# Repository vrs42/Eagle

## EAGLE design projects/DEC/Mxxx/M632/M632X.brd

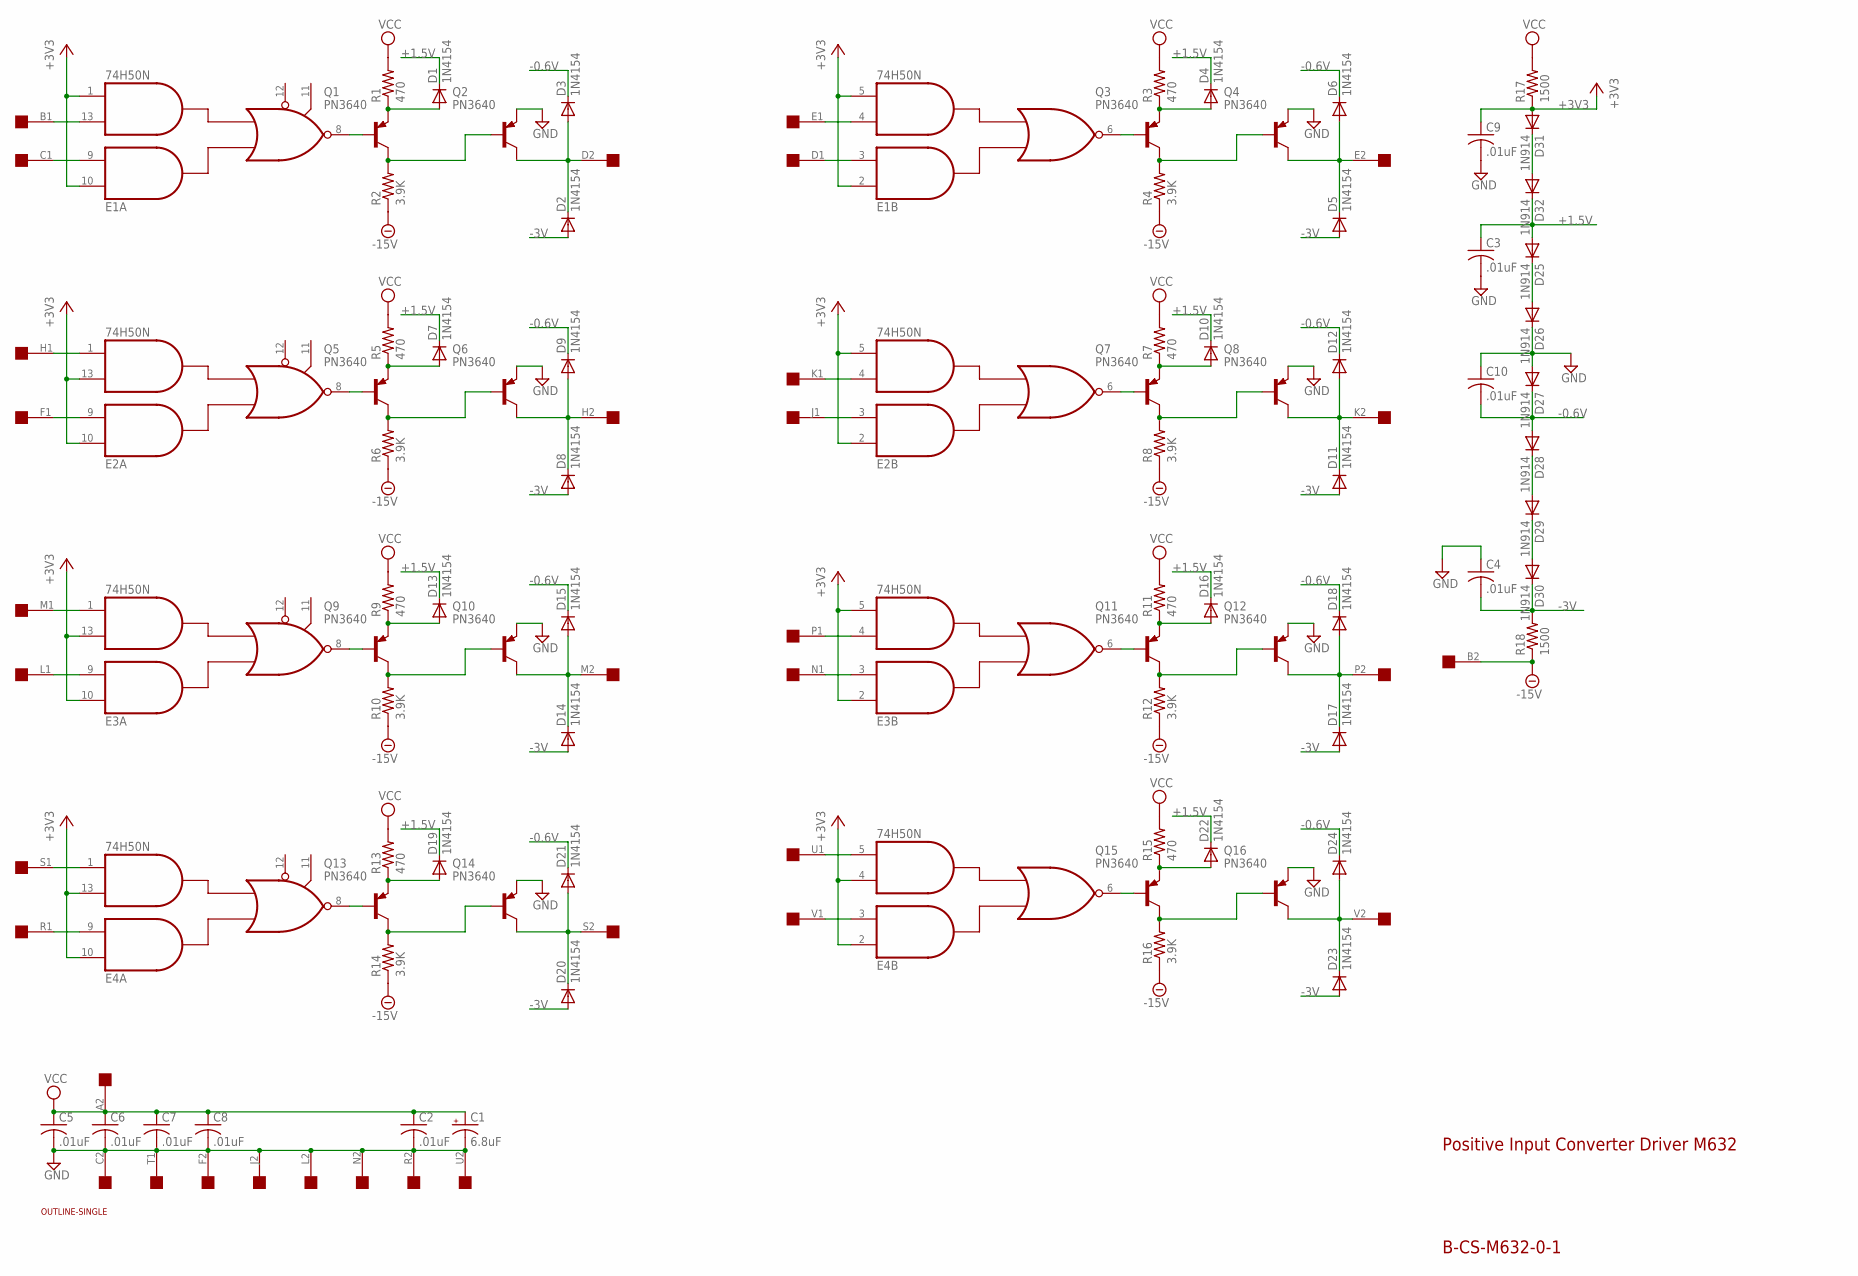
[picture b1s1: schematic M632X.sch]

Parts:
C1: 6.8uF; E12-8
C2, C3, C4, C5, C6, C7, C8, C9, C10: .01uF; C050-025X075
D1, D2, D3, D4, D5, D6, D7, D8, D9, D10, D11, D12, D13, D14, D15, D16, D17, D18, D19, D20, D21, D22, D23, D24: 1N4154; DO35-10
D25, D26, D27, D28, D29, D30, D31, D32: 1N914; DO35-10
E1, E2, E3, E4: 74H50N; DIL14
Q1, Q2, Q3, Q4, Q5, Q6, Q7, Q8, Q9, Q10, Q11, Q12, Q13, Q14, Q15, Q16: PN3640; TO39
R1, R3, R5, R7, R9, R11, R13, R15: 470; 0207/10
R2, R4, R6, R8, R10, R12, R14, R16: 3.9K; 0207/10
R17, R18: 1500; 0207/10
U$1: SINGLE; EDGE-CON2
U$4: OUTLINE-SINGLE; SINGLE

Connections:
+1.5V: C3.1, D1.C, D4.C, D7.C, D10.C, D13.C, D16.C, D19.C, D22.C, D25.A, D32.C
+3V3: C9.1, D31.A, E1.1 (I4), E1.2 (I1), E1.5 (I4), E1.10 (I1), E2.2 (I1), E2.5 (I4), E2.10 (I1), E2.13 (I3), E3.2 (I1), E3.5 (I4), E3.10 (I1), E3.13 (I3), E4.2 (I1), E4.4 (I3), E4.10 (I1), E4.13 (I3), R17.1
-0.6V: C10.2, D3.C, D6.C, D9.C, D12.C, D15.C, D18.C, D21.C, D24.C, D27.C, D28.A
-3V: C4.2, D2.A, D5.A, D8.A, D11.A, D14.A, D17.A, D20.A, D23.A, D30.C, R18.2
-15V: R2.1, R4.1, R6.1, R8.1, R10.1, R12.1, R14.1, R16.1, R18.1, U$1.B2
GND: C1.-, C2.2, C3.2, C4.1, C5.2, C6.2, C7.2, C8.2, C9.2, C10.1, D26.C, D27.A, E1.7 (GND), E2.7 (GND), E3.7 (GND), E4.7 (GND), Q2.1 (E), Q4.1 (E), Q6.1 (E), Q8.1 (E), Q10.1 (E), Q12.1 (E), Q14.1 (E), Q16.1 (E), U$1.C2, U$1.F2, U$1.J2, U$1.L2, U$1.N2, U$1.R2, U$1.T1, U$1.U2
unnamed: E2.3 (I2), U$1.J1
unnamed: E2.4 (I3), U$1.K1
unnamed: E1.9 (I2), U$1.C1
unnamed: E1.13 (I3), U$1.B1
unnamed: E4.1 (I4), U$1.S1
unnamed: E4.9 (I2), U$1.R1
unnamed: E1.8 (O), Q1.2 (B)
unnamed: Q1.3 (C), Q2.2 (B), R2.2
unnamed: E2.8 (O), Q5.2 (B)
unnamed: D7.A, Q5.1 (E), R5.1
unnamed: D2.C, D3.A, Q2.3 (C), U$1.D2
unnamed: Q5.3 (C), Q6.2 (B), R6.2
unnamed: D8.C, D9.A, Q6.3 (C), U$1.H2
unnamed: E4.3 (I2), U$1.V1
unnamed: E4.5 (I4), U$1.U1
unnamed: E3.1 (I4), U$1.M1
unnamed: E3.9 (I2), U$1.L1
unnamed: E3.8 (O), Q9.2 (B)
unnamed: D13.A, Q9.1 (E), R9.1
unnamed: Q9.3 (C), Q10.2 (B), R10.2
unnamed: D14.C, D15.A, Q10.3 (C), U$1.M2
unnamed: E4.8 (O), Q13.2 (B)
unnamed: D19.A, Q13.1 (E), R13.1
unnamed: Q13.3 (C), Q14.2 (B), R14.2
unnamed: D20.C, D21.A, Q14.3 (C), U$1.S2
unnamed: E1.6 (O), Q3.2 (B)
unnamed: D4.A, Q3.1 (E), R3.1
unnamed: Q3.3 (C), Q4.2 (B), R4.2
unnamed: E1.4 (I3), U$1.E1
unnamed: E1.3 (I2), U$1.D1
unnamed: D5.C, D6.A, Q4.3 (C), U$1.E2
unnamed: E2.6 (O), Q7.2 (B)
unnamed: E2.1 (I4), U$1.H1
unnamed: E3.3 (I2), U$1.N1
unnamed: E3.4 (I3), U$1.P1
unnamed: E2.9 (I2), U$1.F1
unnamed: D10.A, Q7.1 (E), R7.1
unnamed: Q7.3 (C), Q8.2 (B), R8.2
unnamed: D11.C, D12.A, Q8.3 (C), U$1.K2
unnamed: E3.6 (O), Q11.2 (B)
unnamed: D1.A, Q1.1 (E), R1.1
unnamed: D16.A, Q11.1 (E), R11.1
unnamed: Q11.3 (C), Q12.2 (B), R12.2
unnamed: D17.C, D18.A, Q12.3 (C), U$1.P2
unnamed: E4.6 (O), Q15.2 (B)
unnamed: D22.A, Q15.1 (E), R15.1
unnamed: Q15.3 (C), Q16.2 (B), R16.2
unnamed: D23.C, D24.A, Q16.3 (C), U$1.V2
unnamed: D25.C, D26.A
unnamed: D28.C, D29.A
unnamed: D31.C, D32.A
unnamed: D29.C, D30.A
VCC: C1.+, C2.1, C5.1, C6.1, C7.1, C8.1, E1.14 (VCC), E2.14 (VCC), E3.14 (VCC), E4.14 (VCC), R1.2, R3.2, R5.2, R7.2, R9.2, R11.2, R13.2, R15.2, R17.2, U$1.A2

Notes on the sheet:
Positive Input Converter Driver M632
B-CS-M632-0-1

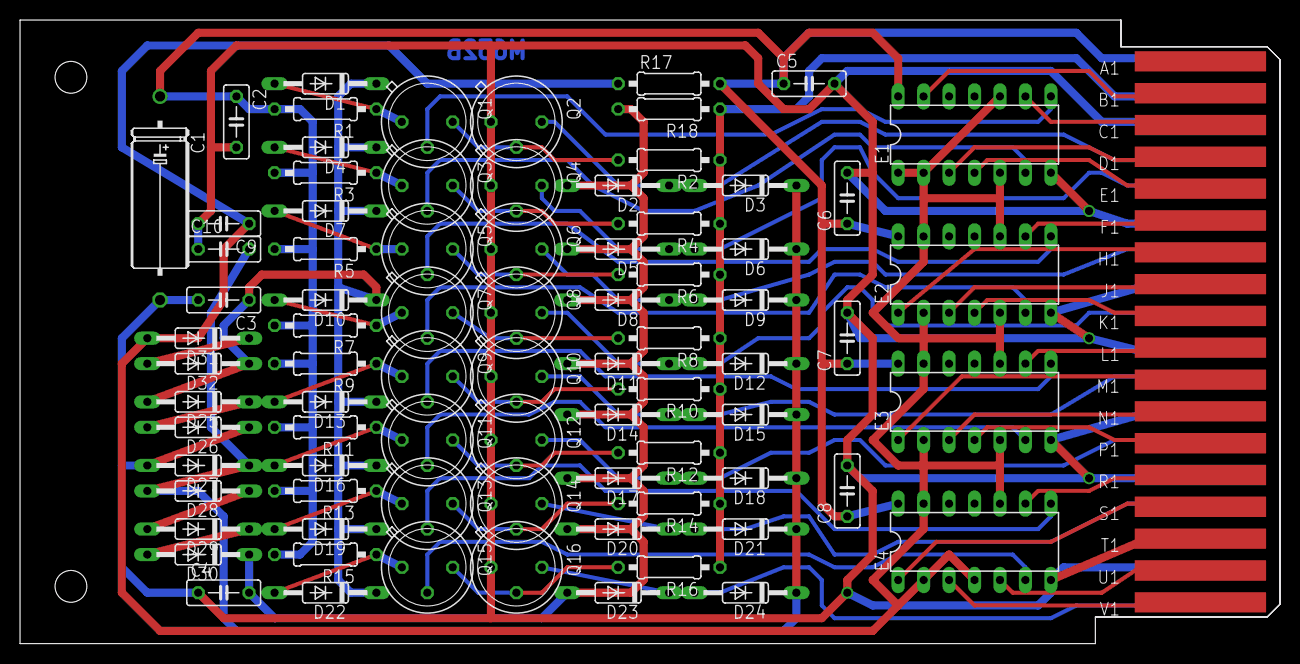
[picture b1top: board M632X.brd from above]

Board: 2 copper layers, 125.7 x 62.2 mm, 82 parts (0 on the bottom side), 59 nets.

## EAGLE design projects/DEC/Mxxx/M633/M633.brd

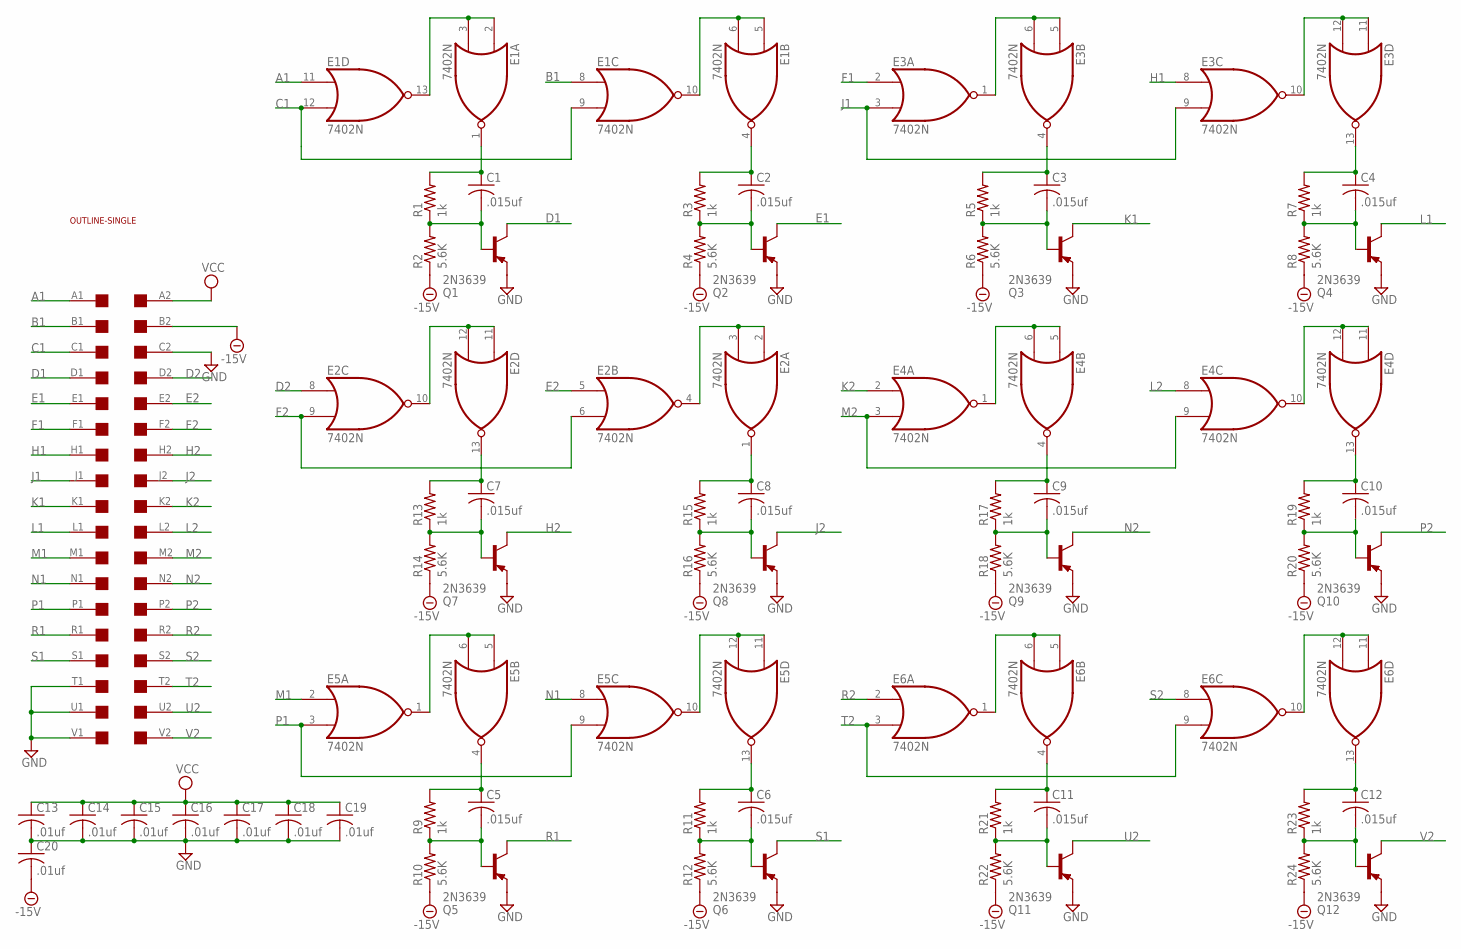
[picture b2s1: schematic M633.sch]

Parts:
C1, C2, C3, C4, C5, C6, C7, C8, C9, C10, C11, C12: .015uf; C050-025X075
C13, C14, C15, C16, C17, C18, C19, C20: .01uf; C050-025X075
E1, E2, E3, E4, E5, E6: 7402N; DIL14
Q1, Q2, Q3, Q4, Q5, Q6, Q7, Q8, Q9, Q10, Q11, Q12: 2N3639; TO39
R1, R3, R5, R7, R9, R11, R13, R15, R17, R19, R21, R23: 1k; 0207/10
R2, R4, R6, R8, R10, R12, R14, R16, R18, R20, R22, R24: 5.6K; 0207/10
U$1: SINGLE; EDGE-CON2
U$2: OUTLINE-SINGLE; SINGLE

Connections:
-15V: C20.2, R2.1, R4.1, R6.1, R8.1, R10.1, R12.1, R14.1, R16.1, R18.1, R20.1, R22.1, R24.1, U$1.B2
A1: E1.11 (I0), U$1.A1
B1: E1.8 (I0), U$1.B1
C1: E1.9 (I1), E1.12 (I1), U$1.C1
D1: Q1.3 (C), U$1.D1
D2: E2.8 (I0), U$1.D2
E1: Q2.3 (C), U$1.E1
E2: E2.5 (I0), U$1.E2
F1: E3.2 (I0), U$1.F1
F2: E2.6 (I1), E2.9 (I1), U$1.F2
GND: C13.2, C14.2, C15.2, C16.2, C17.2, C18.2, C19.2, C20.1, E1.7 (GND), E2.7 (GND), E3.7 (GND), E4.7 (GND), E5.7 (GND), E6.7 (GND), Q1.1 (E), Q2.1 (E), Q3.1 (E), Q4.1 (E), Q5.1 (E), Q6.1 (E), Q7.1 (E), Q8.1 (E), Q9.1 (E), Q10.1 (E), Q11.1 (E), Q12.1 (E), U$1.C2, U$1.T1, U$1.U1, U$1.V1
H1: E3.8 (I0), U$1.H1
H2: Q7.3 (C), U$1.H2
J1: E3.3 (I1), E3.9 (I1), U$1.J1
J2: Q8.3 (C), U$1.J2
K1: Q3.3 (C), U$1.K1
K2: E4.2 (I0), U$1.K2
L1: Q4.3 (C), U$1.L1
L2: E4.8 (I0), U$1.L2
M1: E5.2 (I0), U$1.M1
M2: E4.3 (I1), E4.9 (I1), U$1.M2
N1: E5.8 (I0), U$1.N1
N2: Q9.3 (C), U$1.N2
unnamed: E1.2 (I0), E1.3 (I1), E1.13 (O)
unnamed: C1.1, E1.1 (O), R1.2
unnamed: C1.2, Q1.2 (B), R1.1, R2.2
unnamed: C3.1, E3.4 (O), R5.2
unnamed: C2.1, E1.4 (O), R3.2
unnamed: C2.2, Q2.2 (B), R3.1, R4.2
unnamed: E1.5 (I0), E1.6 (I1), E1.10 (O)
unnamed: E2.10 (O), E2.11 (I0), E2.12 (I1)
unnamed: E2.2 (I0), E2.3 (I1), E2.4 (O)
unnamed: E4.1 (O), E4.5 (I0), E4.6 (I1)
unnamed: E4.10 (O), E4.11 (I0), E4.12 (I1)
unnamed: E6.10 (O), E6.11 (I0), E6.12 (I1)
unnamed: E6.1 (O), E6.5 (I0), E6.6 (I1)
unnamed: E5.10 (O), E5.11 (I0), E5.12 (I1)
unnamed: E5.1 (O), E5.5 (I0), E5.6 (I1)
unnamed: E3.10 (O), E3.11 (I0), E3.12 (I1)
unnamed: E3.1 (O), E3.5 (I0), E3.6 (I1)
unnamed: C4.1, E3.13 (O), R7.2
unnamed: C9.1, E4.4 (O), R17.2
unnamed: C10.1, E4.13 (O), R19.2
unnamed: C8.1, E2.1 (O), R15.2
unnamed: C7.1, E2.13 (O), R13.2
unnamed: C7.2, Q7.2 (B), R13.1, R14.2
unnamed: C8.2, Q8.2 (B), R15.1, R16.2
unnamed: C9.2, Q9.2 (B), R17.1, R18.2
unnamed: C10.2, Q10.2 (B), R19.1, R20.2
unnamed: C5.1, E5.4 (O), R9.2
unnamed: C5.2, Q5.2 (B), R9.1, R10.2
unnamed: C6.2, Q6.2 (B), R11.1, R12.2
unnamed: C11.2, Q11.2 (B), R21.1, R22.2
unnamed: C12.2, Q12.2 (B), R23.1, R24.2
unnamed: C6.1, E5.13 (O), R11.2
unnamed: C11.1, E6.4 (O), R21.2
unnamed: C12.1, E6.13 (O), R23.2
unnamed: C3.2, Q3.2 (B), R5.1, R6.2
unnamed: C4.2, Q4.2 (B), R7.1, R8.2
P1: E5.3 (I1), E5.9 (I1), U$1.P1
P2: Q10.3 (C), U$1.P2
R1: Q5.3 (C), U$1.R1
R2: E6.2 (I0), U$1.R2
S1: Q6.3 (C), U$1.S1
S2: E6.8 (I0), U$1.S2
T2: E6.3 (I1), E6.9 (I1), U$1.T2
U2: Q11.3 (C), U$1.U2
V2: Q12.3 (C), U$1.V2
VCC: C13.1, C14.1, C15.1, C16.1, C17.1, C18.1, C19.1, E1.14 (VCC), E2.14 (VCC), E3.14 (VCC), E4.14 (VCC), E5.14 (VCC), E6.14 (VCC), U$1.A2

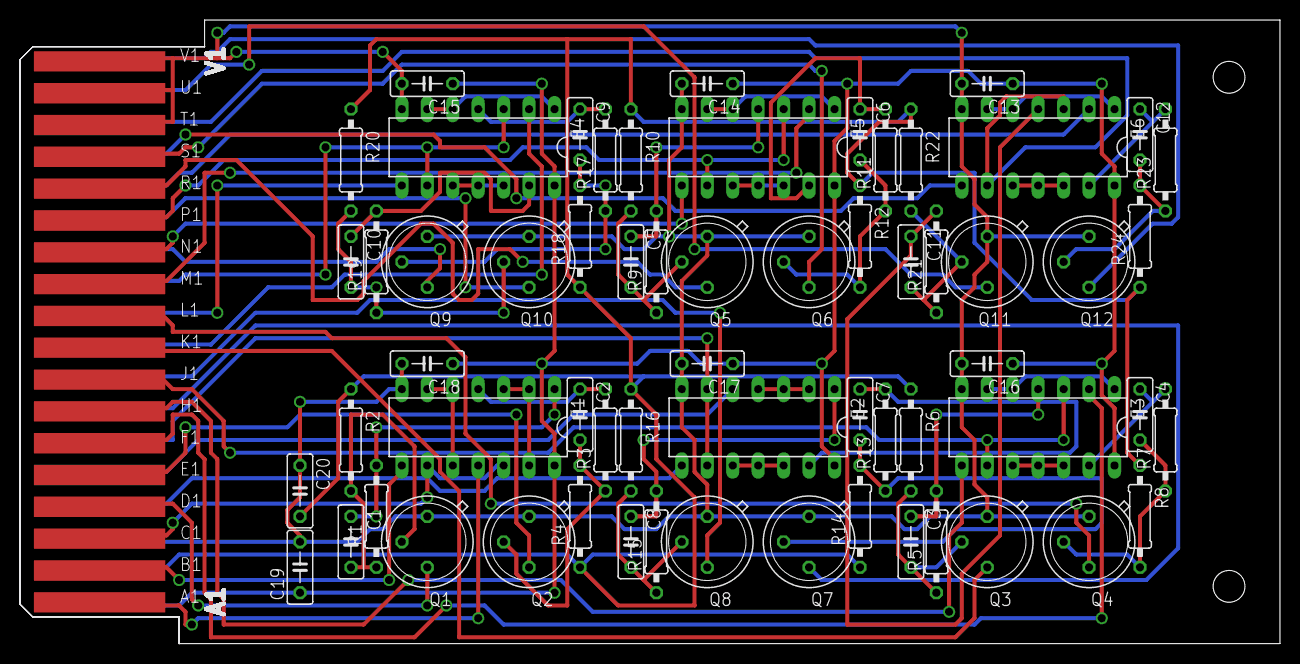
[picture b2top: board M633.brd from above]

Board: 2 copper layers, 125.7 x 62.2 mm, 64 parts (0 on the bottom side), 69 nets.

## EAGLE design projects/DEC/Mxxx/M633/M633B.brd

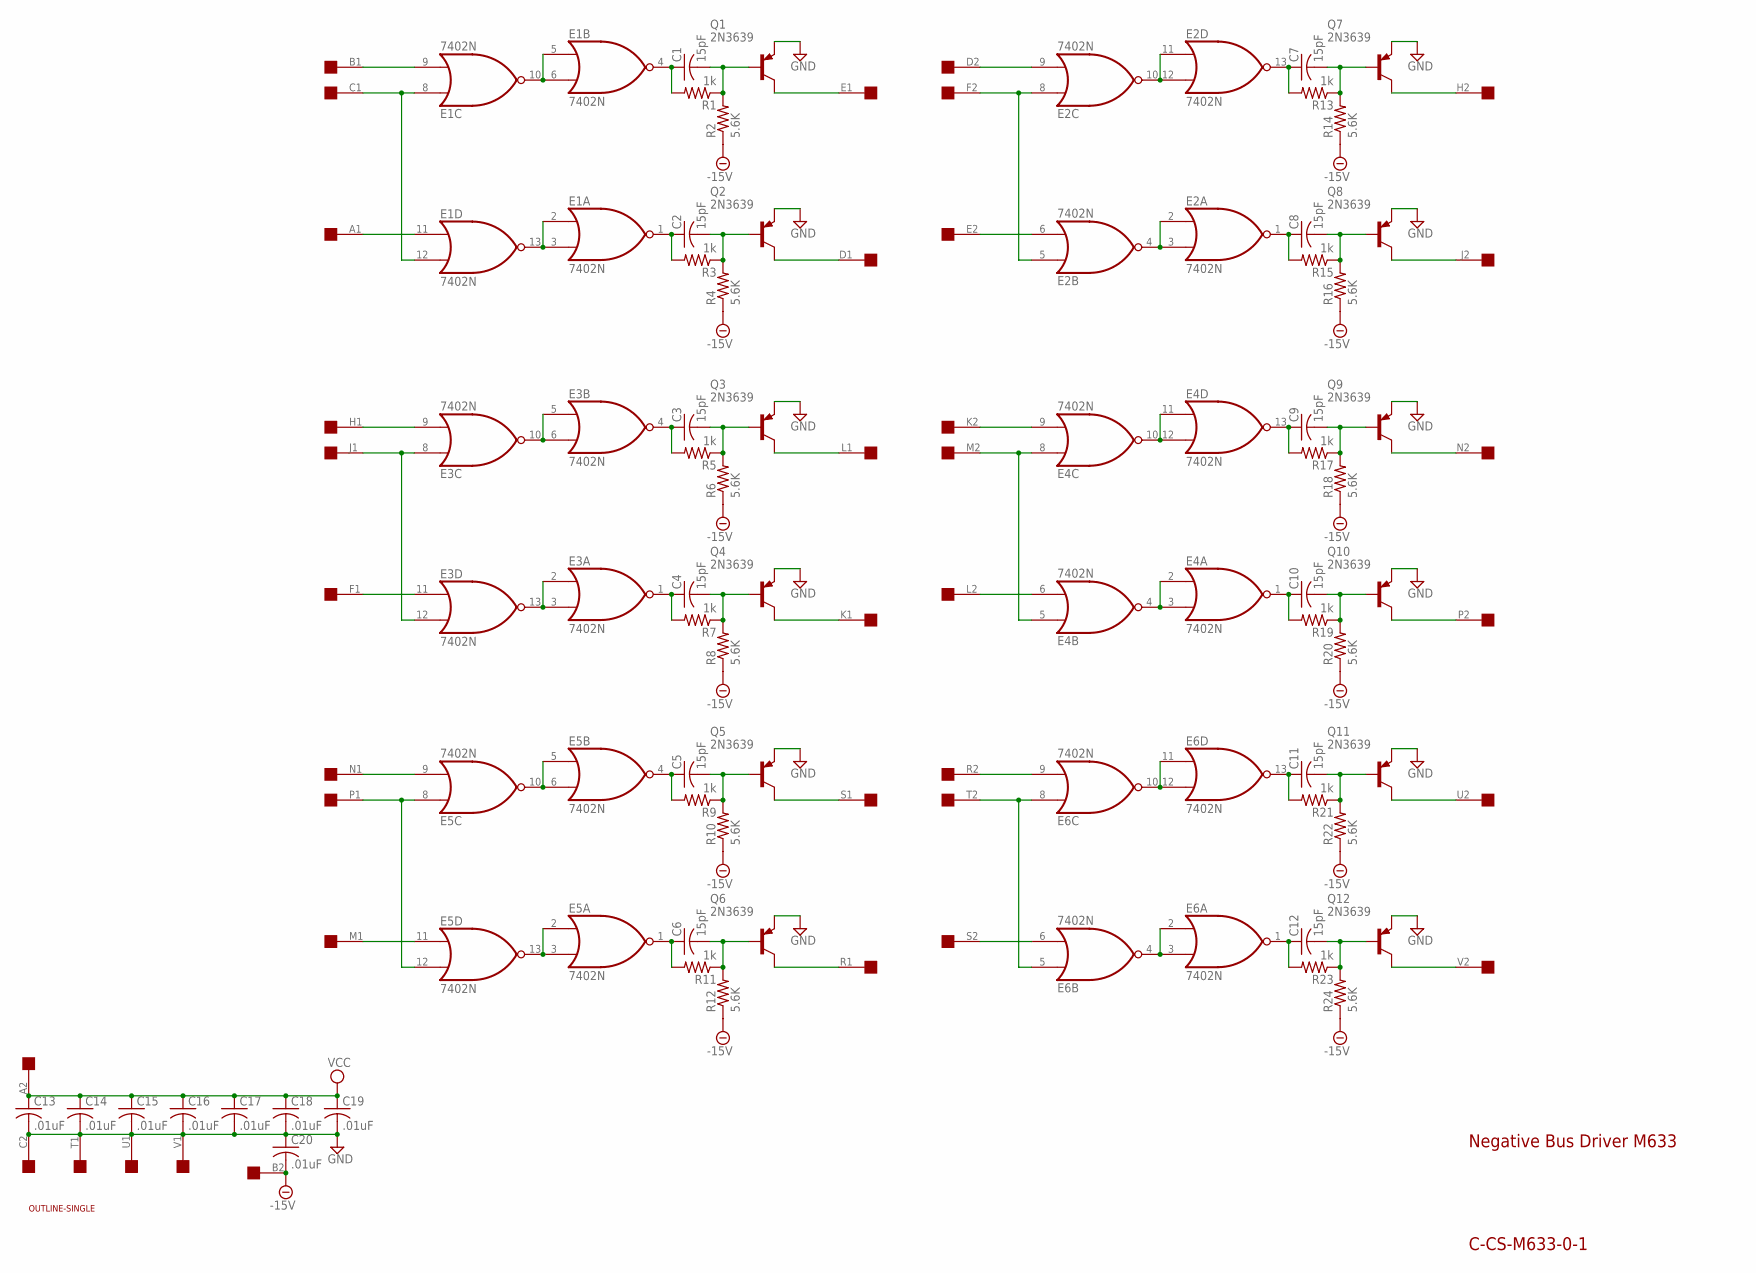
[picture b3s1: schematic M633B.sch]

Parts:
C1, C2, C3, C4, C5, C6, C7, C8, C9, C10, C11, C12: 15pF; C050-025X075
C13, C14, C15, C16, C17, C18, C19, C20: .01uF; C050-025X075
E1, E2, E3, E4, E5, E6: 7402N; DIL14
Q1, Q2, Q3, Q4, Q5, Q6, Q7, Q8, Q9, Q10, Q11, Q12: 2N3639; TO39
R1, R3, R5, R7, R9, R11, R13, R15, R17, R19, R21, R23: 1k; 0207/10
R2, R4, R6, R8, R10, R12, R14, R16, R18, R20, R22, R24: 5.6K; 0207/10
U$1: OUTLINE-SINGLE; SINGLE
U$4: SINGLE; EDGE-CON2

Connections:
-15V: C20.2, R2.1, R4.1, R6.1, R8.1, R10.1, R12.1, R14.1, R16.1, R18.1, R20.1, R22.1, R24.1, U$4.B2
GND: C13.2, C14.2, C15.2, C16.2, C17.2, C18.2, C19.2, C20.1, E1.7 (GND), E2.7 (GND), E3.7 (GND), E4.7 (GND), E5.7 (GND), E6.7 (GND), Q1.1 (E), Q2.1 (E), Q3.1 (E), Q4.1 (E), Q5.1 (E), Q6.1 (E), Q7.1 (E), Q8.1 (E), Q9.1 (E), Q10.1 (E), Q11.1 (E), Q12.1 (E), U$4.C2, U$4.T1, U$4.U1, U$4.V1
unnamed: E1.5 (I0), E1.6 (I1), E1.10 (O)
unnamed: C1.1, E1.4 (O), R1.2
unnamed: C1.2, Q1.2 (B), R1.1, R2.2
unnamed: E1.2 (I0), E1.3 (I1), E1.13 (O)
unnamed: E4.10 (O), E4.11 (I0), E4.12 (I1)
unnamed: C9.1, E4.13 (O), R17.2
unnamed: E4.2 (I0), E4.3 (I1), E4.4 (O)
unnamed: C10.1, E4.1 (O), R19.2
unnamed: C10.2, Q10.2 (B), R19.1, R20.2
unnamed: E4.5 (I0), E4.8 (I0), U$4.M2
unnamed: E4.9 (I1), U$4.K2
unnamed: C2.1, E1.1 (O), R3.2
unnamed: C2.2, Q2.2 (B), R3.1, R4.2
unnamed: E1.8 (I0), E1.12 (I1), U$4.C1
unnamed: E1.9 (I1), U$4.B1
unnamed: E1.11 (I0), U$4.A1
unnamed: Q2.3 (C), U$4.D1
unnamed: Q1.3 (C), U$4.E1
unnamed: E2.10 (O), E2.11 (I0), E2.12 (I1)
unnamed: C7.1, E2.13 (O), R13.2
unnamed: C7.2, Q7.2 (B), R13.1, R14.2
unnamed: E2.2 (I0), E2.3 (I1), E2.4 (O)
unnamed: E4.6 (I1), U$4.L2
unnamed: C8.1, E2.1 (O), R15.2
unnamed: C8.2, Q8.2 (B), R15.1, R16.2
unnamed: E2.5 (I0), E2.8 (I0), U$4.F2
unnamed: E2.9 (I1), U$4.D2
unnamed: E2.6 (I1), U$4.E2
unnamed: Q8.3 (C), U$4.J2
unnamed: Q7.3 (C), U$4.H2
unnamed: E3.5 (I0), E3.6 (I1), E3.10 (O)
unnamed: C3.1, E3.4 (O), R5.2
unnamed: Q10.3 (C), U$4.P2
unnamed: Q9.3 (C), U$4.N2
unnamed: C3.2, Q3.2 (B), R5.1, R6.2
unnamed: C9.2, Q9.2 (B), R17.1, R18.2
unnamed: E3.2 (I0), E3.3 (I1), E3.13 (O)
unnamed: C4.1, E3.1 (O), R7.2
unnamed: C4.2, Q4.2 (B), R7.1, R8.2
unnamed: E3.8 (I0), E3.12 (I1), U$4.J1
unnamed: E3.9 (I1), U$4.H1
unnamed: E3.11 (I0), U$4.F1
unnamed: Q4.3 (C), U$4.K1
unnamed: Q3.3 (C), U$4.L1
unnamed: E5.5 (I0), E5.6 (I1), E5.10 (O)
unnamed: C5.1, E5.4 (O), R9.2
unnamed: C5.2, Q5.2 (B), R9.1, R10.2
unnamed: E5.2 (I0), E5.3 (I1), E5.13 (O)
unnamed: C6.1, E5.1 (O), R11.2
unnamed: C6.2, Q6.2 (B), R11.1, R12.2
unnamed: E5.8 (I0), E5.12 (I1), U$4.P1
unnamed: E5.9 (I1), U$4.N1
unnamed: E5.11 (I0), U$4.M1
unnamed: Q6.3 (C), U$4.R1
unnamed: Q5.3 (C), U$4.S1
unnamed: E6.10 (O), E6.11 (I0), E6.12 (I1)
unnamed: C11.1, E6.13 (O), R21.2
unnamed: C11.2, Q11.2 (B), R21.1, R22.2
unnamed: E6.2 (I0), E6.3 (I1), E6.4 (O)
unnamed: C12.1, E6.1 (O), R23.2
unnamed: C12.2, Q12.2 (B), R23.1, R24.2
unnamed: E6.5 (I0), E6.8 (I0), U$4.T2
unnamed: E6.9 (I1), U$4.R2
unnamed: E6.6 (I1), U$4.S2
unnamed: Q12.3 (C), U$4.V2
unnamed: Q11.3 (C), U$4.U2
VCC: C13.1, C14.1, C15.1, C16.1, C17.1, C18.1, C19.1, E1.14 (VCC), E2.14 (VCC), E3.14 (VCC), E4.14 (VCC), E5.14 (VCC), E6.14 (VCC), U$4.A2

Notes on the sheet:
Negative Bus Driver M633
C-CS-M633-0-1

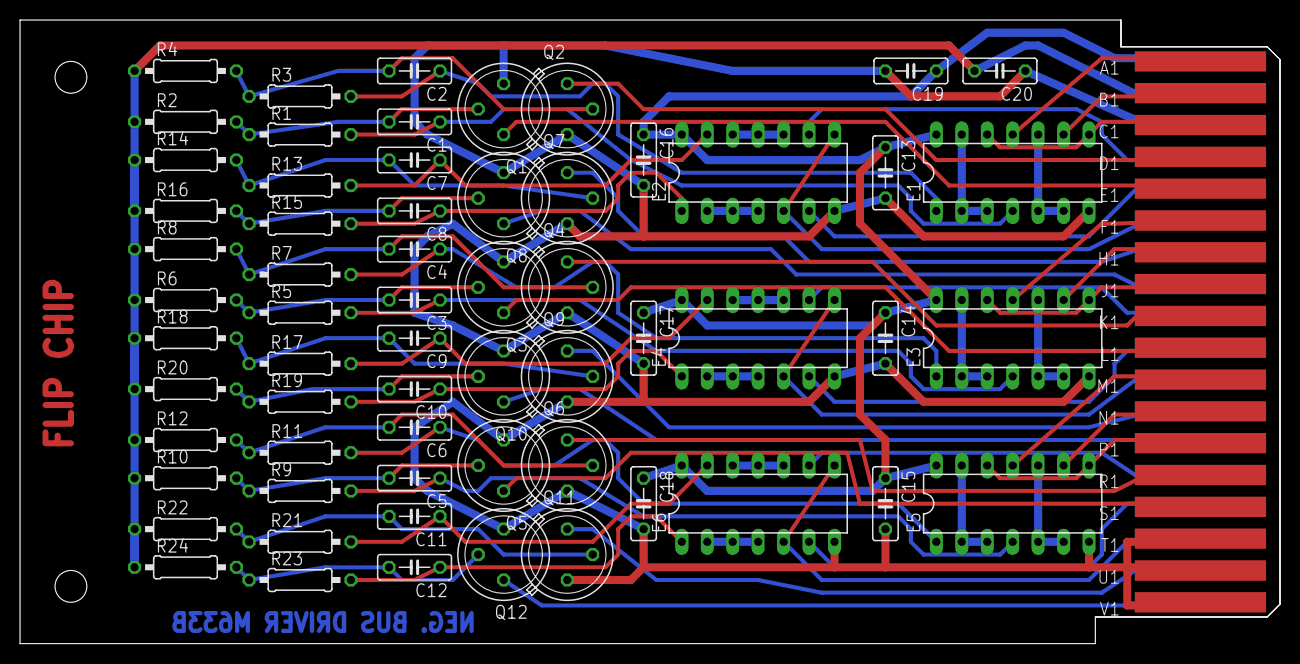
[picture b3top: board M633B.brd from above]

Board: 2 copper layers, 125.7 x 62.2 mm, 65 parts (0 on the bottom side), 69 nets.

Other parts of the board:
U$2: FLIPCHIP

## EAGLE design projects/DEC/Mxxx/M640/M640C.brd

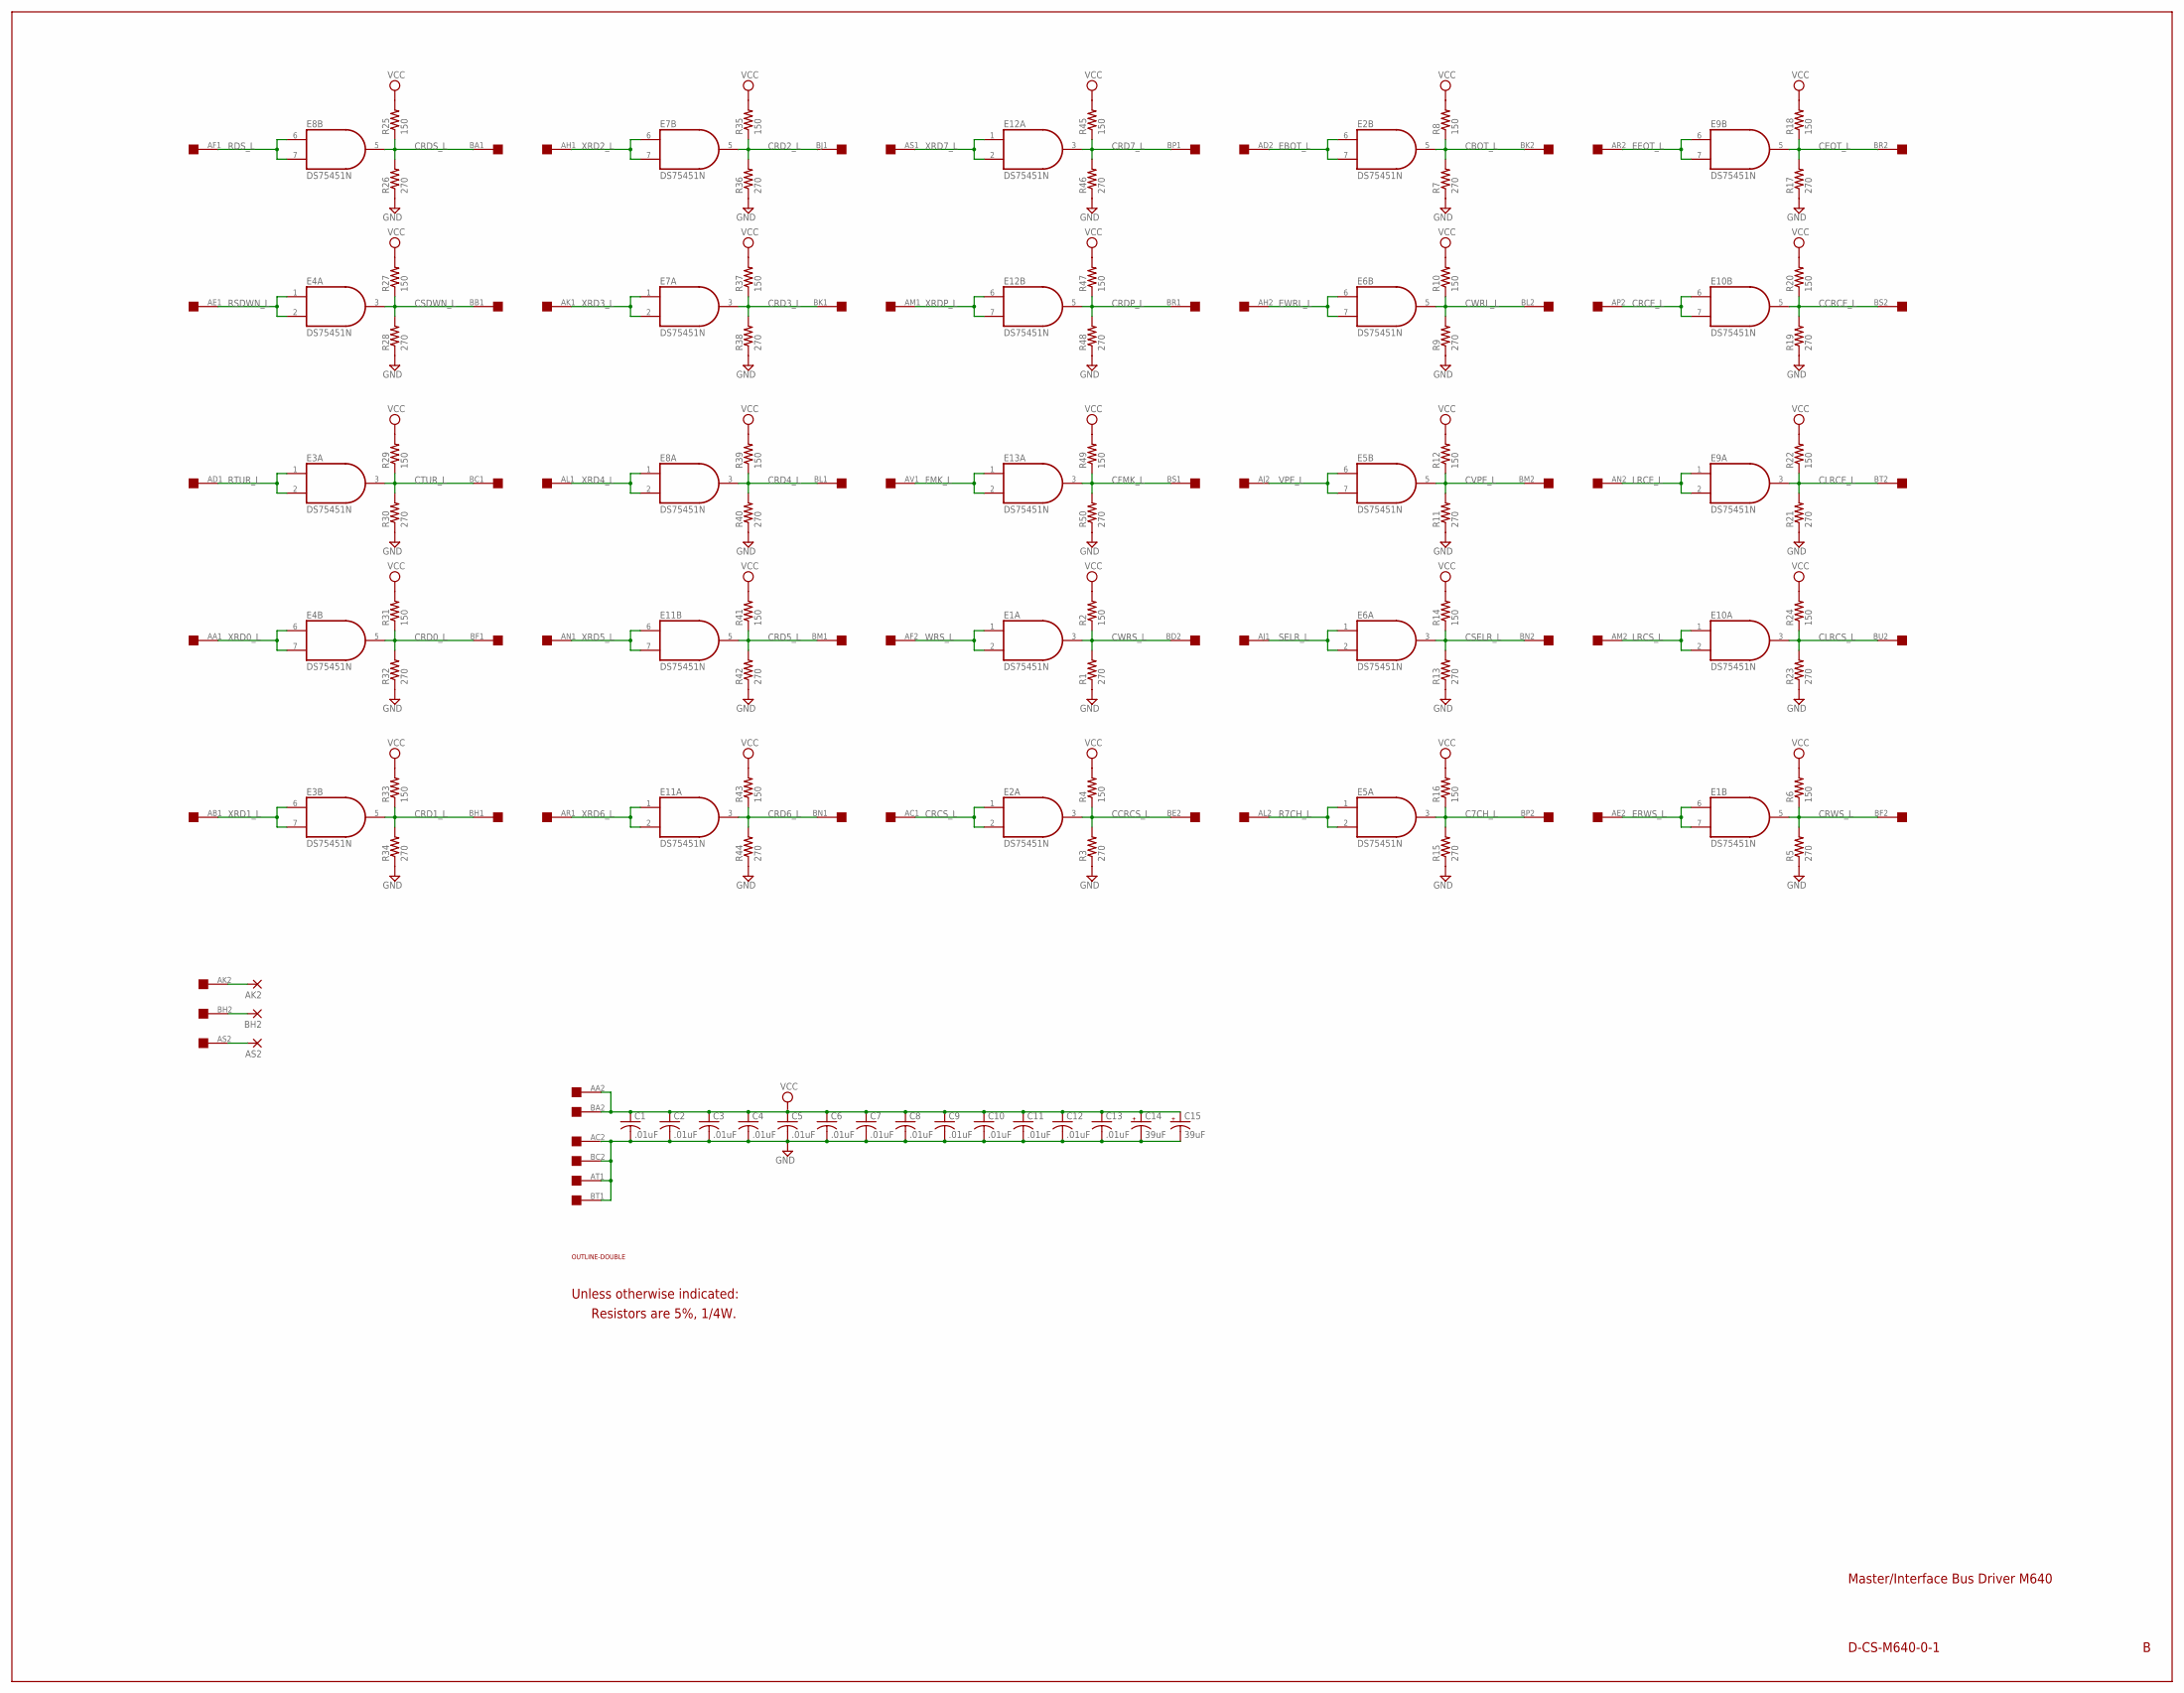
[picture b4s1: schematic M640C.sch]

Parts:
AK2: 1,6/0,8
AS2: 1,6/0,8
BH2: 1,6/0,8
C1, C2, C3, C4, C5, C6, C7, C8, C9, C10, C11, C12, C13: .01uF; C050-025X075
C14, C15: 39uF; E12-8
E1, E2, E3, E4, E5, E6, E7, E8, E9, E10, E11, E12, E13: DS75451N; DIL08
R1, R3, R5, R7, R9, R11, R13, R15, R17, R19, R21, R23, R26, R28, R30, R32, R34, R36, R38, R40, R42, R44, R46, R48, R50: 270; 0207/10
R2, R4, R6, R8, R10, R12, R14, R16, R18, R20, R22, R24, R25, R27, R29, R31, R33, R35, R37, R39, R41, R43, R45, R47, R49: 150; 0207/10
U$1: DOUBLE; EDGE-CON4
U$2: OUTLINE-DOUBLE; DOUBLE

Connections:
C7CH_L: E5.3 (O), R15.2, R16.1, U$1.BP2
CBOT_L: E2.5 (O), R7.2, R8.1, U$1.BK2
CCRCE_L: E10.5 (O), R19.2, R20.1, U$1.BS2
CCRCS_L: E2.3 (O), R3.2, R4.1, U$1.BE2
CEOT_L: E9.5 (O), R17.2, R18.1, U$1.BR2
CFMK_L: E13.3 (O), R49.1, R50.2, U$1.BS1
CLRCE_L: E9.3 (O), R21.2, R22.1, U$1.BT2
CLRCS_L: E10.3 (O), R23.2, R24.1, U$1.BU2
CRCE_L: E10.6 (I0), E10.7 (I1), U$1.AP2
CRCS_L: E2.1 (I0), E2.2 (I1), U$1.AC1
CRD0_L: E4.5 (O), R31.1, R32.2, U$1.BF1
CRD1_L: E3.5 (O), R33.1, R34.2, U$1.BH1
CRD2_L: E7.5 (O), R35.1, R36.2, U$1.BJ1
CRD3_L: E7.3 (O), R37.1, R38.2, U$1.BK1
CRD4_L: E8.3 (O), R39.1, R40.2, U$1.BL1
CRD5_L: E11.5 (O), R41.1, R42.2, U$1.BM1
CRD6_L: E11.3 (O), R43.1, R44.2, U$1.BN1
CRD7_L: E12.3 (O), R45.1, R46.2, U$1.BP1
CRDP_L: E12.5 (O), R47.1, R48.2, U$1.BR1
CRDS_L: E8.5 (O), R25.1, R26.2, U$1.BA1
CRWS_L: E1.5 (O), R5.2, R6.1, U$1.BF2
CSDWN_L: E4.3 (O), R27.1, R28.2, U$1.BB1
CSELR_L: E6.3 (O), R13.2, R14.1, U$1.BN2
CTUR_L: E3.3 (O), R29.1, R30.2, U$1.BC1
CVPE_L: E5.5 (O), R11.2, R12.1, U$1.BM2
CWRL_L: E6.5 (O), R9.2, R10.1, U$1.BL2
CWRS_L: E1.3 (O), R1.2, R2.1, U$1.BD2
EBOT_L: E2.6 (I0), E2.7 (I1), U$1.AD2
EEOT_L: E9.6 (I0), E9.7 (I1), U$1.AR2
ERWS_L: E1.6 (I0), E1.7 (I1), U$1.AE2
EWRL_L: E6.6 (I0), E6.7 (I1), U$1.AH2
FMK_L: E13.1 (I0), E13.2 (I1), U$1.AV1
GND: C1.2, C2.2, C3.2, C4.2, C5.2, C6.2, C7.2, C8.2, C9.2, C10.2, C11.2, C12.2, C13.2, C14.-, C15.-, E1.4 (GND), E2.4 (GND), E3.4 (GND), E4.4 (GND), E5.4 (GND), E6.4 (GND), E7.4 (GND), E8.4 (GND), E9.4 (GND), E10.4 (GND), E11.4 (GND), E12.4 (GND), E13.4 (GND), R1.1, R3.1, R5.1, R7.1, R9.1, R11.1, R13.1, R15.1, R17.1, R19.1, R21.1, R23.1, R26.1, R28.1, R30.1, R32.1, R34.1, R36.1, R38.1, R40.1, R42.1, R44.1, R46.1, R48.1, R50.1, U$1.AC2, U$1.AT1, U$1.BC2, U$1.BT1
LRCE_L: E9.1 (I0), E9.2 (I1), U$1.AN2
LRCS_L: E10.1 (I0), E10.2 (I1), U$1.AM2
unnamed: AK2.1, U$1.AK2
unnamed: BH2.1, U$1.BH2
unnamed: AS2.1, U$1.AS2
R7CH_L: E5.1 (I0), E5.2 (I1), U$1.AL2
RDS_L: E8.6 (I0), E8.7 (I1), U$1.AF1
RSDWN_L: E4.1 (I0), E4.2 (I1), U$1.AE1
RTUR_L: E3.1 (I0), E3.2 (I1), U$1.AD1
SELR_L: E6.1 (I0), E6.2 (I1), U$1.AJ1
VCC: C1.1, C2.1, C3.1, C4.1, C5.1, C6.1, C7.1, C8.1, C9.1, C10.1, C11.1, C12.1, C13.1, C14.+, C15.+, E1.8 (VCC), E2.8 (VCC), E3.8 (VCC), E4.8 (VCC), E5.8 (VCC), E6.8 (VCC), E7.8 (VCC), E8.8 (VCC), E9.8 (VCC), E10.8 (VCC), E11.8 (VCC), E12.8 (VCC), E13.8 (VCC), R2.2, R4.2, R6.2, R8.2, R10.2, R12.2, R14.2, R16.2, R18.2, R20.2, R22.2, R24.2, R25.2, R27.2, R29.2, R31.2, R33.2, R35.2, R37.2, R39.2, R41.2, R43.2, R45.2, R47.2, R49.2, U$1.AA2, U$1.BA2
VPE_L: E5.6 (I0), E5.7 (I1), U$1.AJ2
WRS_L: E1.1 (I0), E1.2 (I1), U$1.AF2
XRD0_L: E4.6 (I0), E4.7 (I1), U$1.AA1
XRD1_L: E3.6 (I0), E3.7 (I1), U$1.AB1
XRD2_L: E7.6 (I0), E7.7 (I1), U$1.AH1
XRD3_L: E7.1 (I0), E7.2 (I1), U$1.AK1
XRD4_L: E8.1 (I0), E8.2 (I1), U$1.AL1
XRD5_L: E11.6 (I0), E11.7 (I1), U$1.AN1
XRD6_L: E11.1 (I0), E11.2 (I1), U$1.AR1
XRD7_L: E12.1 (I0), E12.2 (I1), U$1.AS1
XRDP_L: E12.6 (I0), E12.7 (I1), U$1.AM1

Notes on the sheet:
Master/Interface Bus Driver M640
D-CS-M640-0-1
Unless otherwise indicated:
Resistors are 5%, 1/4W.

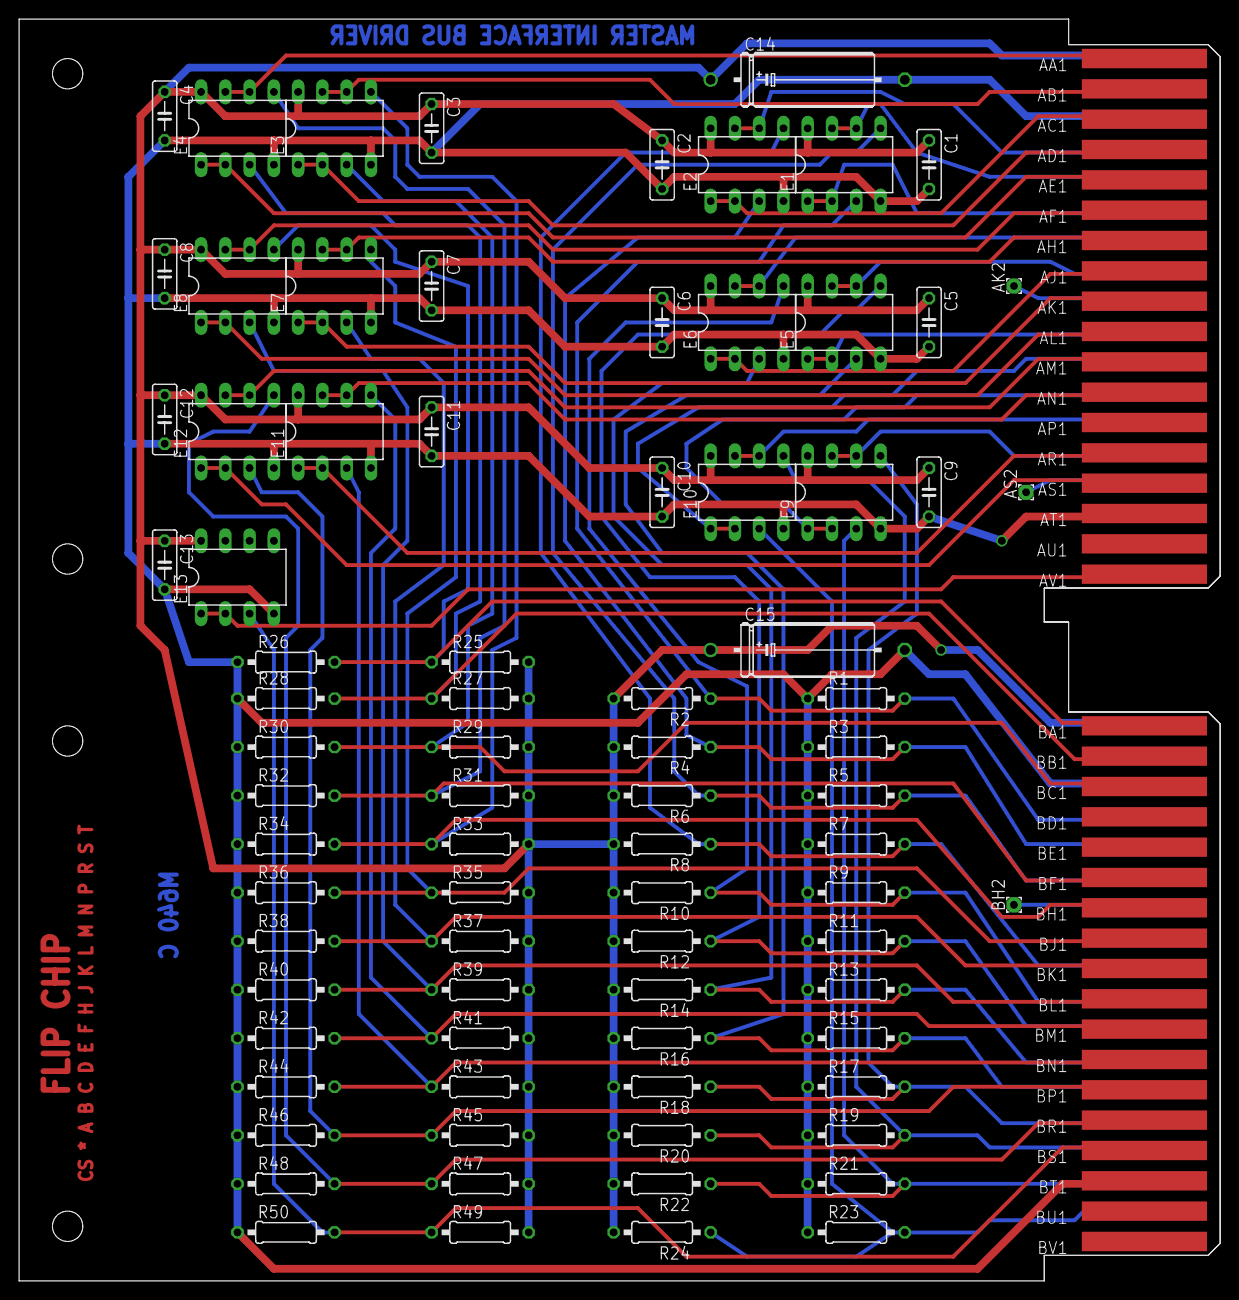
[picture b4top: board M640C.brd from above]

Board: 2 copper layers, 125.7 x 132.1 mm, 84 parts (0 on the bottom side), 55 nets.

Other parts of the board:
U$4: FLIPCHIP
